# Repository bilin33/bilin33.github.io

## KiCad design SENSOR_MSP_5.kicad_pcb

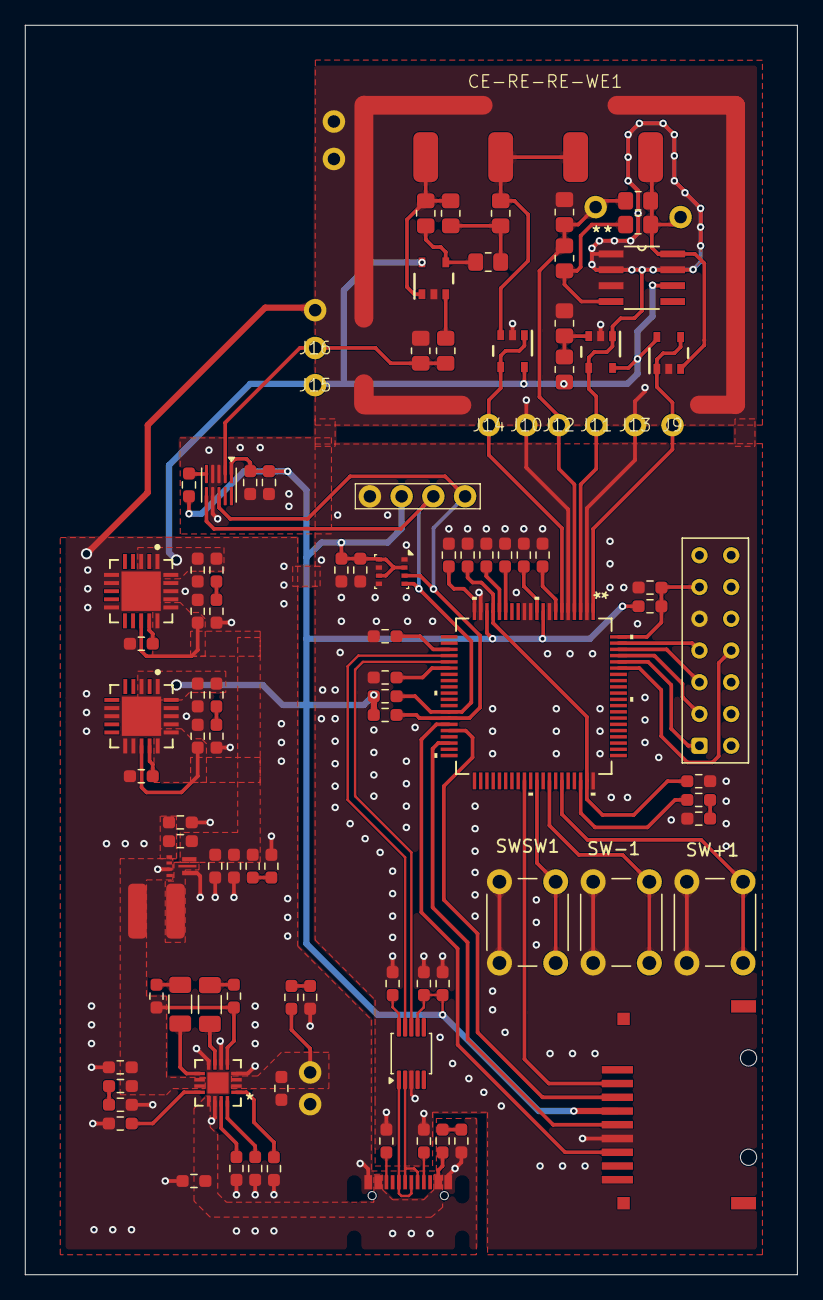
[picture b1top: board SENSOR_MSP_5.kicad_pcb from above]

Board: 2 copper layers, 61.8 x 100.0 mm, 107 parts (0 on the bottom side), 71 nets.

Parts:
BME1: BME280; Bosch_LGA-8_2.5x2.5mm_P0.65mm_ClockwisePinNumbering
BQ1: BQ24074RGTT
BT1: Battery; CONNECTOR2
C1, C12, C14, C22, C23: 0.1uF; R_0603_1608Metric_Pad0.98x0.95mm_HandSolder
C2, C3, C4, C5, C6, C7, C8: 0.47uF; R_0603_1608Metric_Pad0.98x0.95mm_HandSolder
C9: 0.01uF; R_0603_1608Metric_Pad0.98x0.95mm_HandSolder
C10, C24, C26: 4.7uF; R_0603_1608Metric_Pad0.98x0.95mm_HandSolder
C11, C13, C21, C25, C31, C33: 1uF; R_0603_1608Metric_Pad0.98x0.95mm_HandSolder
C17: 10nF; R_0805_2012Metric_Pad1.20x1.40mm_HandSolder
C18: 1nF; R_0805_2012Metric_Pad1.20x1.40mm_HandSolder
C19: 5pF; R_0805_2012Metric_Pad1.20x1.40mm_HandSolder
C20: 100pF; R_0805_2012Metric_Pad1.20x1.40mm_HandSolder
C28, C29: 22uF; R_0603_1608Metric_Pad0.98x0.95mm_HandSolder
C30, C34: 10uF; R_0603_1608Metric_Pad0.98x0.95mm_HandSolder
C32, C35: 47uF; R_0603_1608Metric_Pad0.98x0.95mm_HandSolder
CE-RE-RE-WE1: Conn_01x04_Socket; ELECTRODE
D1, D2: 1N4148WT; R_1206_3216Metric_Pad1.30x1.75mm_HandSolder
D3, D4, D5, D6, D7, D8, D9: LED; R_0603_1608Metric_Pad0.98x0.95mm_HandSolder
J1: Conn_02x07_Counter_Clockwise; Samtec_HLE-107-02-xx-DV-TE_2x07_P2.54mm_Horizontal
J2: Micro_SD_Card_Det1; SDSOCKET
J3, J4, J5, J6, J7, J9, J10, J11, J12, J13, J14, J15, J16: Conn_01x01_Socket; CONNECTOR1
J8: RFShield_TwoPieces; MS300-10F
L1: 1uH; 74404043010A
R1, R2, R3, R4, R18: 10K; R_0805_2012Metric_Pad1.20x1.40mm_HandSolder
R5, R6: 1M; R_0805_2012Metric_Pad1.20x1.40mm_HandSolder
R7, R8: 5.1K; R_0603_1608Metric_Pad0.98x0.95mm_HandSolder
R9: 10K; R_0603_1608Metric_Pad0.98x0.95mm_HandSolder
R10, R11: 1.5K; R_0603_1608Metric_Pad0.98x0.95mm_HandSolder
R12: 1.13K; R_0603_1608Metric_Pad0.98x0.95mm_HandSolder
R13: 4.12K; R_0603_1608Metric_Pad0.98x0.95mm_HandSolder
R14: 1.18K; R_0603_1608Metric_Pad0.98x0.95mm_HandSolder
R15: 750k; R_0603_1608Metric_Pad0.98x0.95mm_HandSolder
R16: 100K; R_0603_1608Metric_Pad0.98x0.95mm_HandSolder
R17: 30K; R_0805_2012Metric_Pad1.20x1.40mm_HandSolder
R19, R20, R21, R22, R23, R24, R25: R_US; R_0603_1608Metric_Pad0.98x0.95mm_HandSolder
RSCLUP1: 47K; R_0603_1608Metric_Pad0.98x0.95mm_HandSolder
RSD1: 10K; R_0603_1608Metric_Pad0.98x0.95mm_HandSolder
RSDAUP1: 47K; R_0603_1608Metric_Pad0.98x0.95mm_HandSolder
RSTUP1: 47K; R_0603_1608Metric_Pad0.98x0.95mm_HandSolder
SSD1: SCREEN
SW+1: SW_Push_Open_Dual; SW_PUSH_6mm
SW-1: SW_Push_Open_Dual; SW_PUSH_6mm
SWSW1: SW_Push_Open_Dual; SW_PUSH_6mm
TPS1: TPS61022RWUR
U1: MSP430F6736AIPNR
U2: DAC80502; Texas_DRX_WSON-10_2.5x2.5mm_P0.5mm
U3, U4, U5, U9: OPA189IDBVR; OPA189
U6: CH340E; MSOP-10_3x3mm_P0.5mm
U7, U8: TPS7A4700RGWR; TPS7A4700RGW0020A-IPC_A
U10: LMP7721MA/NOPB; LMP7721M08A
typec1: TYPEC16PIN

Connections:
/CSN: J2.2 (DAT3/CD), U1.49 (P4.0/S23)
/DVSYS: C5.1, C10.1, U1.17 (VDSYS), U1.59 (DVSYS)
/KEY+1: SW+1.1, SW+1.2, U1.55 (P4.6/S17)
/KEY-1: SW-1.1, SW-1.2, U1.53 (P4.4/S19)
/KEYSW: SWSW1.1, SWSW1.2, U1.51 (P4.2/S21)
/MISO: J2.7 (DAT0), U1.35 (P2.2/PM_UCA2RXD/PM_UCA2SOMI/S37)
/MOSI: J2.3 (CMD), U1.36 (P2.3/PM_UCA2TXD/PM_UCA2SIMO/S36)
/OPA380/CE: C17.2, C18.2, CE-RE-RE-WE1.1, U3.1 (OUT)
/OPA380/RE: CE-RE-RE-WE1.2, CE-RE-RE-WE1.3, R1.1, U5.3 (IN+)
/OPA380/WE: C19.1, CE-RE-RE-WE1.4, J6.1 (Pin_1_1), R5.1, U4.3 (IN+), U10.8 (IN-)
/RST: C9.1, J1.11, RSTUP1.2, U1.80 (*RST/NMI/SBWTDIO)
/SCL: BME1.4 (SCK), RSCLUP1.1, SSD1.3 (SCL), U1.33 (P2.0/PM_UCB0SOMI/PM_UCB0SCL/COM6/S39), U2.6 (SCLK/SCL)
/SCLK: J2.5 (CLK), U1.38 (P2.5/PM_UCA2CLK/S34)
/SDA: BME1.3 (SDI), RSDAUP1.1, SSD1.4 (SDA), U1.34 (P2.1/PM_UCB0SIMO/PM_UCB0SDA/COM7/S38), U2.8 (SDIN/SDA)
/TCK: J1.7, U1.79 (PJ.3/ACLK/TCK)
/TDI: J1.3, U1.77 (PJ.1/MCLK/TDI/TCLK)
/TDO: J1.1, U1.76 (PJ.0/SMCLK/TDO)
/TEST: J1.8, U1.75 (TEST/SBWTCK)
/TMS: J1.5, U1.78 (PJ.2/ADC10CLK/TMS)
/charge/BQOUT: BQ1.5 (EN2), BQ1.10 (OUT), BQ1.11 (OUT), C26.1, L1.1, R10.1, R11.1, R21.1, TPS1.5 (EN), TPS1.7 (VIN)
/charge/BTOUT: BQ1.2 (BAT), BQ1.3 (BAT), BT1.1 (+), C24.1, R20.1
/charge/TPSOUT: C28.1, C29.1, C30.1, C34.1, R15.2, R22.1, TPS1.3 (VOUT), U7.13 (EN), U7.15 (IN), U7.16 (IN), U8.13 (EN), U8.15 (IN), U8.16 (IN)
/charge/TYPEC_OUT: BQ1.13 (IN), C25.1, R19.1, typec1.A4 (VBUS), typec1.B4 (VBUS)
/charge/UD+: U6.1 (UD+), typec1.A6 (DP1), typec1.B6 (DP2)
/charge/UD-: U6.2 (UD-), typec1.A7 (DN1), typec1.B7 (DN2)
DAC_OUT: J16.1 (Pin_1_1), R3.1, R4.2, U2.2 (VOUTA)
GND: BME1.1 (GND), BME1.5 (SDO), BME1.7 (GND), BQ1.4 (*CE), BQ1.6 (EN1), BQ1.8 (VSS), BQ1.14 (TMR), BQ1.17 (EPAD), BT1.2 (-), C1.2, C2.2, C3.2, C4.2, C5.2, C6.2, C7.2, C8.2, C9.2, C10.2, C11.2, C12.2, C13.2, C14.2, C20.2, C21.2, C22.2, C23.2, C24.2, C25.2, C26.2, C28.2, C29.2, C30.2, C31.2, C32.2, C33.2, C34.2, C35.2, D3.1 (K), D4.1 (K), D5.1 (K), D6.1 (K), D7.1 (K), D8.1 (K), D9.1 (K), J1.9, J2.6 (VSS), J3.1 (Pin_1_1), J4.1 (Pin_1_1), J5.1 (Pin_1_1), J8.1 (Shield_1), J10.1 (Pin_1_1), J13.1 (Pin_1_1), R3.2, R7.2, R8.2, R9.1, R12.2, R13.2, R14.2, R16.2, R18.1, SSD1.1 (GND), SW+1.3, SW+1.4, SW-1.3, SW-1.4, SWSW1.3, SWSW1.4, TPS1.1 (GND), TPS1.6 (MODE), U1.2 (SD0N0), U1.5 (SD2P0), U1.8 (AVSS), U1.11 (P1.0/PM_TA0.0/VeREF-/A2), U1.12 (P1.1/PM_TA0.1/VeREF+/A1), U1.19 (DVSS), U1.60 (DVSS), U2.3 (RSTSEL), U2.4 (AGND), U2.7 (~SYNC/A0), U3.2 (V-), U4.2 (V-), U5.2 (V-), U6.3 (GND), U7.6 (3P2V), U7.7 (GND), U7.10 (0P4V), U7.17 (NC), U7.18 (NC), U7.19 (NC), U7.21 (Thermal_Pad), U8.7 (GND), U8.8 (1P6V), U8.11 (0P2V), U8.12 (0P1V), U8.17 (NC), U8.18 (NC), U8.19 (NC), U8.21 (Thermal_Pad), U9.2 (V-), U10.3 (V-), typec1.A1 (GND), typec1.B1 (GND)
IO58: R25.1, U1.58 (P5.1/S14)
unnamed: BQ1.9 (*CHG), D2.1 (K)
unnamed: BQ1.7 (*PGOOD), D1.1 (K)
unnamed: BQ1.12 (ILIM), R14.1
unnamed: BQ1.16 (ISET), R12.1
unnamed: BQ1.15 (ITERM), R13.1
unnamed: BQ1.1 (TS), R9.2
unnamed: C17.1, R1.2, R2.1
unnamed: D1.2 (A), R10.2
unnamed: D2.2 (A), R11.2
unnamed: D3.2 (A), R19.2
unnamed: D4.2 (A), R20.2
unnamed: D5.2 (A), R21.2
unnamed: D6.2 (A), R22.2
unnamed: D7.2 (A), R23.2
unnamed: D8.2 (A), R24.2
unnamed: D9.2 (A), R25.2
unnamed: R15.1, R16.1, TPS1.4 (FB)
unnamed: L1.2, TPS1.2 (SW)
unnamed: C4.1, U1.16 (AUXVCC1)
unnamed: C3.1, U1.15 (AUXVCC2)
unnamed: C7.1, U1.23 (AUXVCC3)
unnamed: C8.1, U1.26 (LCDCAP/R33)
unnamed: C2.1, U1.10 (VASYS)
unnamed: C6.1, U1.20 (VCORE)
unnamed: C1.1, U1.7 (VREF)
unnamed: RSD1.2, U2.5 (SPI2C)
unnamed: R4.1, U3.3 (IN+)
unnamed: C18.1, R2.2, U3.4 (IN-)
unnamed: C23.1, U6.10 (V3)
unnamed: C31.1, U7.14 (NR)
unnamed: C33.1, U8.14 (NR)
unnamed: R17.1, R18.2, U9.3 (IN+)
unnamed: C19.2, R6.1, U10.4 (OUT)
unnamed: R7.1, typec1.A5 (CC1)
unnamed: R8.1, typec1.B5 (CC2)
RXD: U1.24 (P1.4/PM_UCA1RXD/PM_UCA1SOMI/LCDREF/R13), U6.9 (RXD)
TXD: U1.25 (P1.5/PM_UCA1TXD/PM_UCA1SIMO/R23), U6.8 (TXD)
VCC_1V25: J11.1 (Pin_1_1), U1.3 (SD1P0), U9.1 (OUT), U9.4 (IN-), U10.1 (IN+), U10.2 (NC), U10.7 (NC)
VCC_3V3: BME1.2 (CSB), BME1.6 (VDDIO), BME1.8 (VDD), C11.1, C12.1, C13.1, C14.1, C21.1, C22.1, C35.1, J2.4 (VDD), R24.1, RSCLUP1.2, RSD1.1, RSDAUP1.2, RSTUP1.1, SSD1.2 (VCC), U1.9 (AVCC), U1.18 (DVCC), U2.1 (VDD), U6.7 (VCC), U8.1 (OUT), U8.3 (SENSE_FB), U8.20 (OUT)
VCC_5V: C32.1, J15.1 (Pin_1_1), R17.2, R23.1, U3.5 (V+), U4.5 (V+), U5.5 (V+), U7.1 (OUT), U7.3 (SENSE_FB), U7.20 (OUT), U9.5 (V+), U10.6 (V+)
VOUT380: C20.1, J7.1 (Pin_1_1), J12.1 (Pin_1_1), R5.2, R6.2, U1.4 (SD1N0)
VOUTRE: J14.1 (Pin_1_1), U1.6 (SD2N0), U5.1 (OUT), U5.4 (IN-)
VOUTWE: J9.1 (Pin_1_1), U1.1 (SD0P0), U4.1 (OUT), U4.4 (IN-)

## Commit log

2026-04-07 Create CNAME
2026-05-27 Rename SENSOR_MSP_5.kicad_pcb to hardware/SENSOR_MSP_5.kicad_pcb
2026-05-27 Rename SENSOR_MSP_5.kicad_sch to hardware/SENSOR_MSP_5.kicad_sch
2026-05-27 Rename bme280.c to Software/MSP430F6736A/bme280.c
2026-05-27 Rename bme280.h to Software/MSP430F6736A/bme280.h
2026-05-27 Rename bme280_defs.h to Software/MSP430F6736A /bme280_defs.h
2026-05-27 Rename bme280_defs.h to bme280_defs.h
2026-05-27 Rename bme280_port.c to Software/MSP430F6736A/bme280_port.c
2026-05-27 Rename bme280_port.h to Software/MSP430F6736A/bme280_port.h
2026-05-27 Rename dac80502_ll.c to Software/MSP430F6736A/dac80502_ll.c
2026-05-27 Rename dac80502_ll.h to Software/MSP430F6736A/dac80502_ll.h
2026-05-27 Rename font6x8.c to Software/MSP430F6736A/font6x8.c
2026-05-27 Rename font6x8.h to Software/MSP430F6736A/font6x8.h
2026-05-27 Rename i2c0.c to Software/MSP430F6736A/i2c0.c
2026-05-27 Rename i2c0.h to Software/MSP430F6736A/i2c0.h
2026-05-27 Rename main.c to Software/MSP430F6736A/main.c
2026-05-27 Rename oled_ssd1306_ll.c to Software/MSP430F6736A/oled_ssd1306_ll.c
2026-05-27 Rename oled_ssd1306_ll.h to Software/MSP430F6736A/oled_ssd1306_ll.h
2026-05-27 Rename platform.c to Software/MSP430F6736A/platform.c
2026-05-27 Rename platform.h to Software/MSP430F6736A/platform.h
2026-05-27 Rename sd24_3ch.c to Software/MSP430F6736A/sd24_3ch.c
2026-05-27 Rename sd24_3ch.h to Software/MSP430F6736A/sd24_3ch.h
2026-05-27 Rename uart1.c to Software/MSP430F6736A/uart1.c
2026-05-27 Rename uart1.h to Software/MSP430F6736A/uart1.h
2026-05-27 Rename UARTAPP.py to Software/PC Software/UARTAPP.py
2026-05-27 Rename msp430_data.csv to CSV/msp430_data.csv
2026-05-27 Rename Screenshot 2026-05-22 160602.png to PNG/Screenshot 2026-05-22 160602.png
2026-05-27 Rename Screenshot 2026-05-22 160602.png to CH340E.png
